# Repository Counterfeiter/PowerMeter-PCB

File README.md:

PowerMeter Schematic and PCB Files
==============

License
--------------
OSH - GPLv2

Software
--------------
Free Version of CADSoft Eagle v6 (.1)

Included
--------------
- versions history
- zipped farbication files (gerber, drill files)
- schematic
- PCB design
- Mouser BOM

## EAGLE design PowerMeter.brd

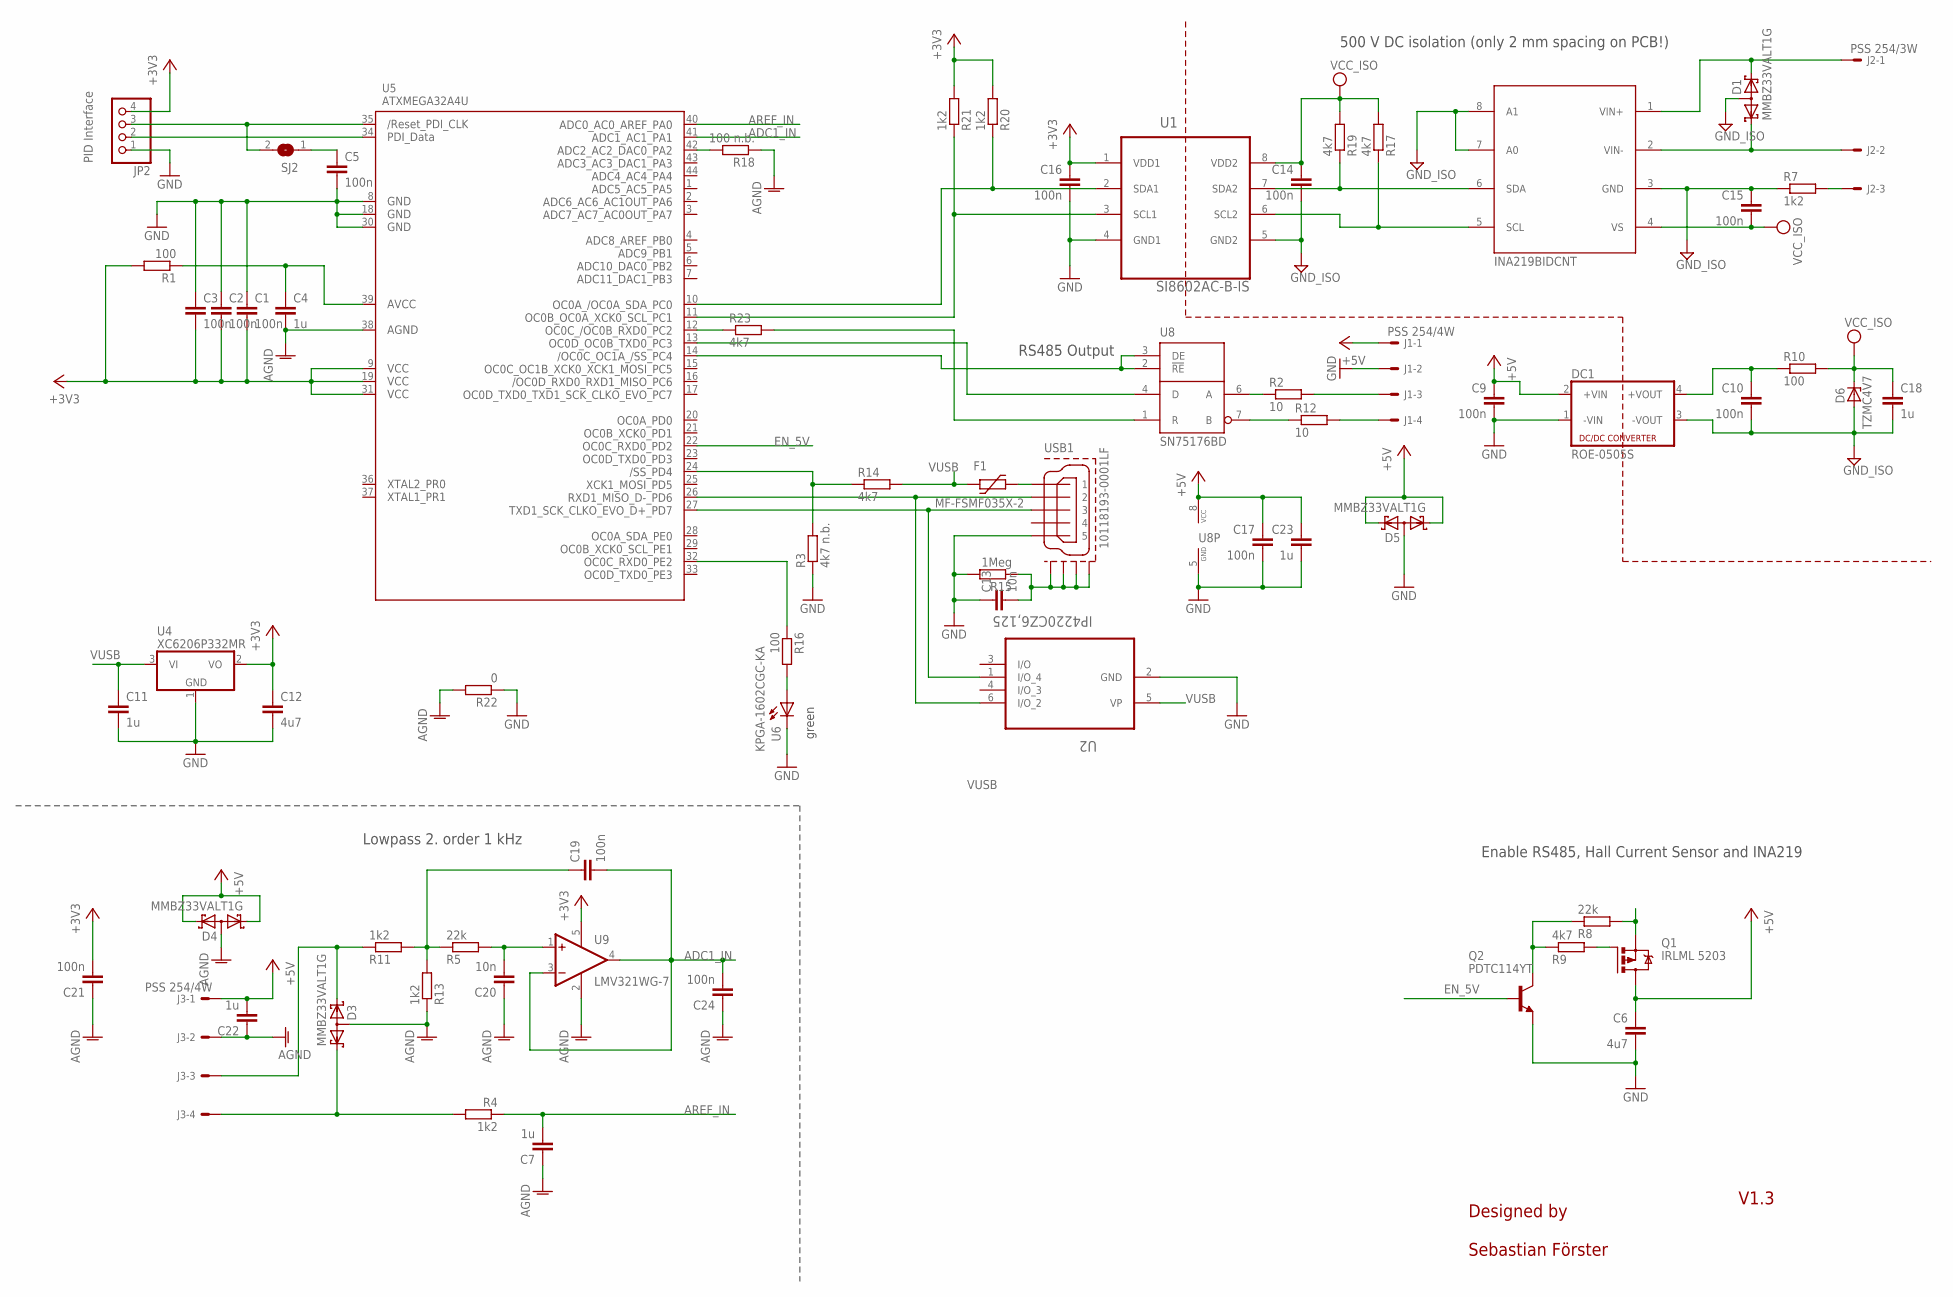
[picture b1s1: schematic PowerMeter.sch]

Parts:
C1, C2, C3, C5, C9, C10, C14, C15, C16, C17, C19, C21, C24: 100n; C0603
C4, C7, C11, C18, C22, C23: 1u; C0603
C6, C12: 4u7; C0603
C13, C20: 10n; C0603
D1, D3, D4, D5: MMBZ33VALT1G; SOT23
D6: TZMC4V7; SOD80C
DC1: ROE-0505S; NME
F1: MF-FSMF035X-2; R0603
J1, J3: PSS 254/4W; 6410-04
J2: PSS 254/3W; 6410-03
JP2: PINHD-1X4_2.00; 1X04M
Q1: IRLML 5203; MICRO3
Q2: PDTC114YT; SOT23
R1, R10, R16: 100; R0603
R2, R12: 10; R0603
R3: 4k7 n.b.; R0603
R4, R7, R11, R13, R20, R21: 1k2; R0603
R5, R8: 22k; R0603
R9, R14, R17, R19, R23: 4k7; R0603
R15: 1Meg; R0603
R18: 100 n.b.; R0603
R22: 0; R0603
SJ2: SJ
U1: SI8602AC-B-IS; SOIC127P600X175-8N
U2: IP4220CZ6,125; SOT95P275X110-6N
U4: XC6206P332MR; SOT23
U5: ATXMEGA32A4U; TQFP44
U6: KPGA-1602CGC-KA; CHIP-LED0603
U7: INA219BIDCNT; SOT23-6
U8: SN75176BD; SO-08
U9: LMV321WG-7; SOT23-5
USB1: 10118193-0001LF; MOLEX-47364-0001

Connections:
+3V3: C1.2, C2.2, C3.2, C12.1, C16.1, C21.2, JP2.4, R1.2, R20.2, R21.2, U1.1 (VDD1), U4.2 (VO), U5.9 (VCC1), U5.19 (VCC2), U5.31 (VCC3), U9.5 (V+)
+5V: C6.1, C9.1, C17.1, C22.2, C23.1, D4.1 (K1), D4.2 (K2), D5.1 (K1), D5.2 (K2), DC1.2 (+VIN), J1.1, J3.1, Q1.3 (D), U8.8 (VCC)
ADC1_IN: C19.2, C24.2, U5.41 (PA1), U9.3 (-IN), U9.4 (OUT)
AGND: C4.2, C7.1, C20.1, C21.1, C22.1, C24.1, D3.3 (AA), D4.3 (AA), J3.2, R13.1, R18.1, R22.2, U5.38 (AGND), U9.2 (V-)
AREF_IN: C7.2, R4.1, U5.40 (PA0)
EN_5V: Q2.1 (B), U5.22 (PD2)
GND: C1.1, C2.1, C3.1, C5.2, C6.2, C9.2, C11.2, C12.2, C13.1, C16.2, C17.2, C23.2, D5.3 (AA), DC1.1 (-VIN), J1.2, JP2.1, Q2.2 (E), R3.1, R15.2, R22.1, U1.4 (GND1), U2.2 (GND), U4.1 (GND), U5.8 (GND1), U5.18 (GND2), U5.30 (GND3), U6.C, U8.5 (GND), USB1.5
GND1: C10.2, C14.2, C15.1, C18.2, D1.3 (AA), D6.A, DC1.3 (-VOUT), R7.1, U1.5 (GND2), U7.3 (GND), U7.7 (A0), U7.8 (A1)
GPS_ENABLE: Q2.3 (C), R8.1, R9.1
unnamed: R23.2, U8.1 (R)
unnamed: D1.1 (K1), J2.2, U7.2 (VIN-)
unnamed: R20.1, U1.2 (SDA1), U5.10 (PC0)
unnamed: J2.3, R7.2
unnamed: R3.2, R14.1, U5.24 (PD4)
unnamed: D1.2 (K2), J2.1, U7.1 (VIN+)
unnamed: C5.1, SJ2.1
unnamed: C4.1, R1.1, U5.39 (AVCC)
unnamed: JP2.3, SJ2.2, U5.35 (RESET)
unnamed: JP2.2, U5.34 (PDI_DATA)
unnamed: C20.2, R5.2, U9.1 (+IN)
unnamed: R12.1, U8.7 (B)
unnamed: Q1.1 (G), R9.2
unnamed: F1.2, USB1.1
unnamed: J1.3, R2.2
unnamed: R2.1, U8.6 (A)
unnamed: J1.4, R12.2
unnamed: U5.13 (PC3), U8.4 (D)
unnamed: D3.1 (K1), J3.4, R4.2
unnamed: C13.2, R15.1, USB1.GND1, USB1.GND2, USB1.GND3, USB1.GND4
unnamed: U2.6 (I/O_2), U5.26 (PD6), USB1.2
unnamed: C19.1, R5.1, R11.2, R13.2
unnamed: U2.1 (I/O_4), U5.27 (PD7), USB1.3
unnamed: D3.2 (K2), J3.3, R11.1
unnamed: R16.2, U6.A
unnamed: R21.1, U1.3 (SCL1), U5.11 (PC1)
unnamed: U5.14 (PC4), U8.2 (!RE), U8.3 (DE)
unnamed: R17.1, U1.6 (SCL2), U7.5 (SCL)
unnamed: R19.1, U1.7 (SDA2), U7.6 (SDA)
unnamed: R18.2, U5.42 (PA2)
unnamed: R23.1, U5.12 (PC2)
unnamed: R16.1, U5.32 (PE2)
VCC: C14.1, C15.2, C18.1, D6.C, R10.2, R17.2, R19.2, U1.8 (VDD2), U7.4 (VS)
VCC_ISO: C10.1, DC1.4 (+VOUT), R10.1
VUSB: C11.1, F1.1, Q1.2 (S), R8.2, R14.2, U2.5 (VP), U4.3 (VI)

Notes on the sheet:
PID Interface
Designed by
Sebastian Förster
green
INA219BIDCNT
V1.3
Lowpass 2. order 1 kHz
Enable RS485, Hall Current Sensor and INA219
RS485 Output
500 V DC isolation (only 2 mm spacing on PCB!)

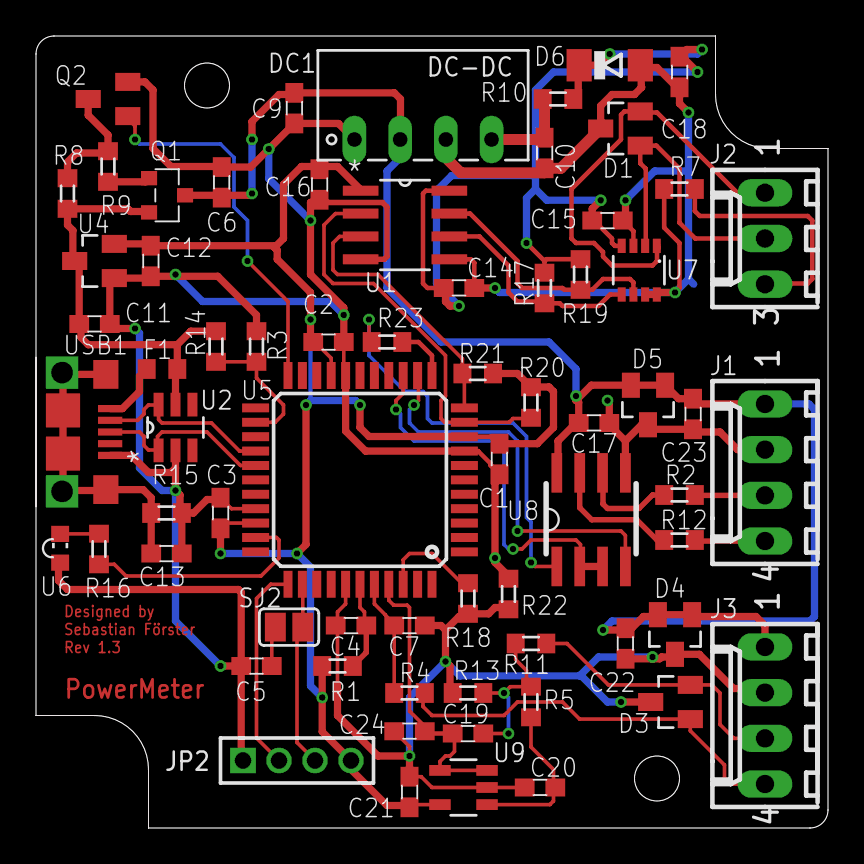
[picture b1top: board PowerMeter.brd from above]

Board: 2 copper layers, 44.0 x 44.0 mm, 68 parts (0 on the bottom side), 44 nets.

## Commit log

2015-04-04 init commit
2016-02-09 - added BOM for mouser
